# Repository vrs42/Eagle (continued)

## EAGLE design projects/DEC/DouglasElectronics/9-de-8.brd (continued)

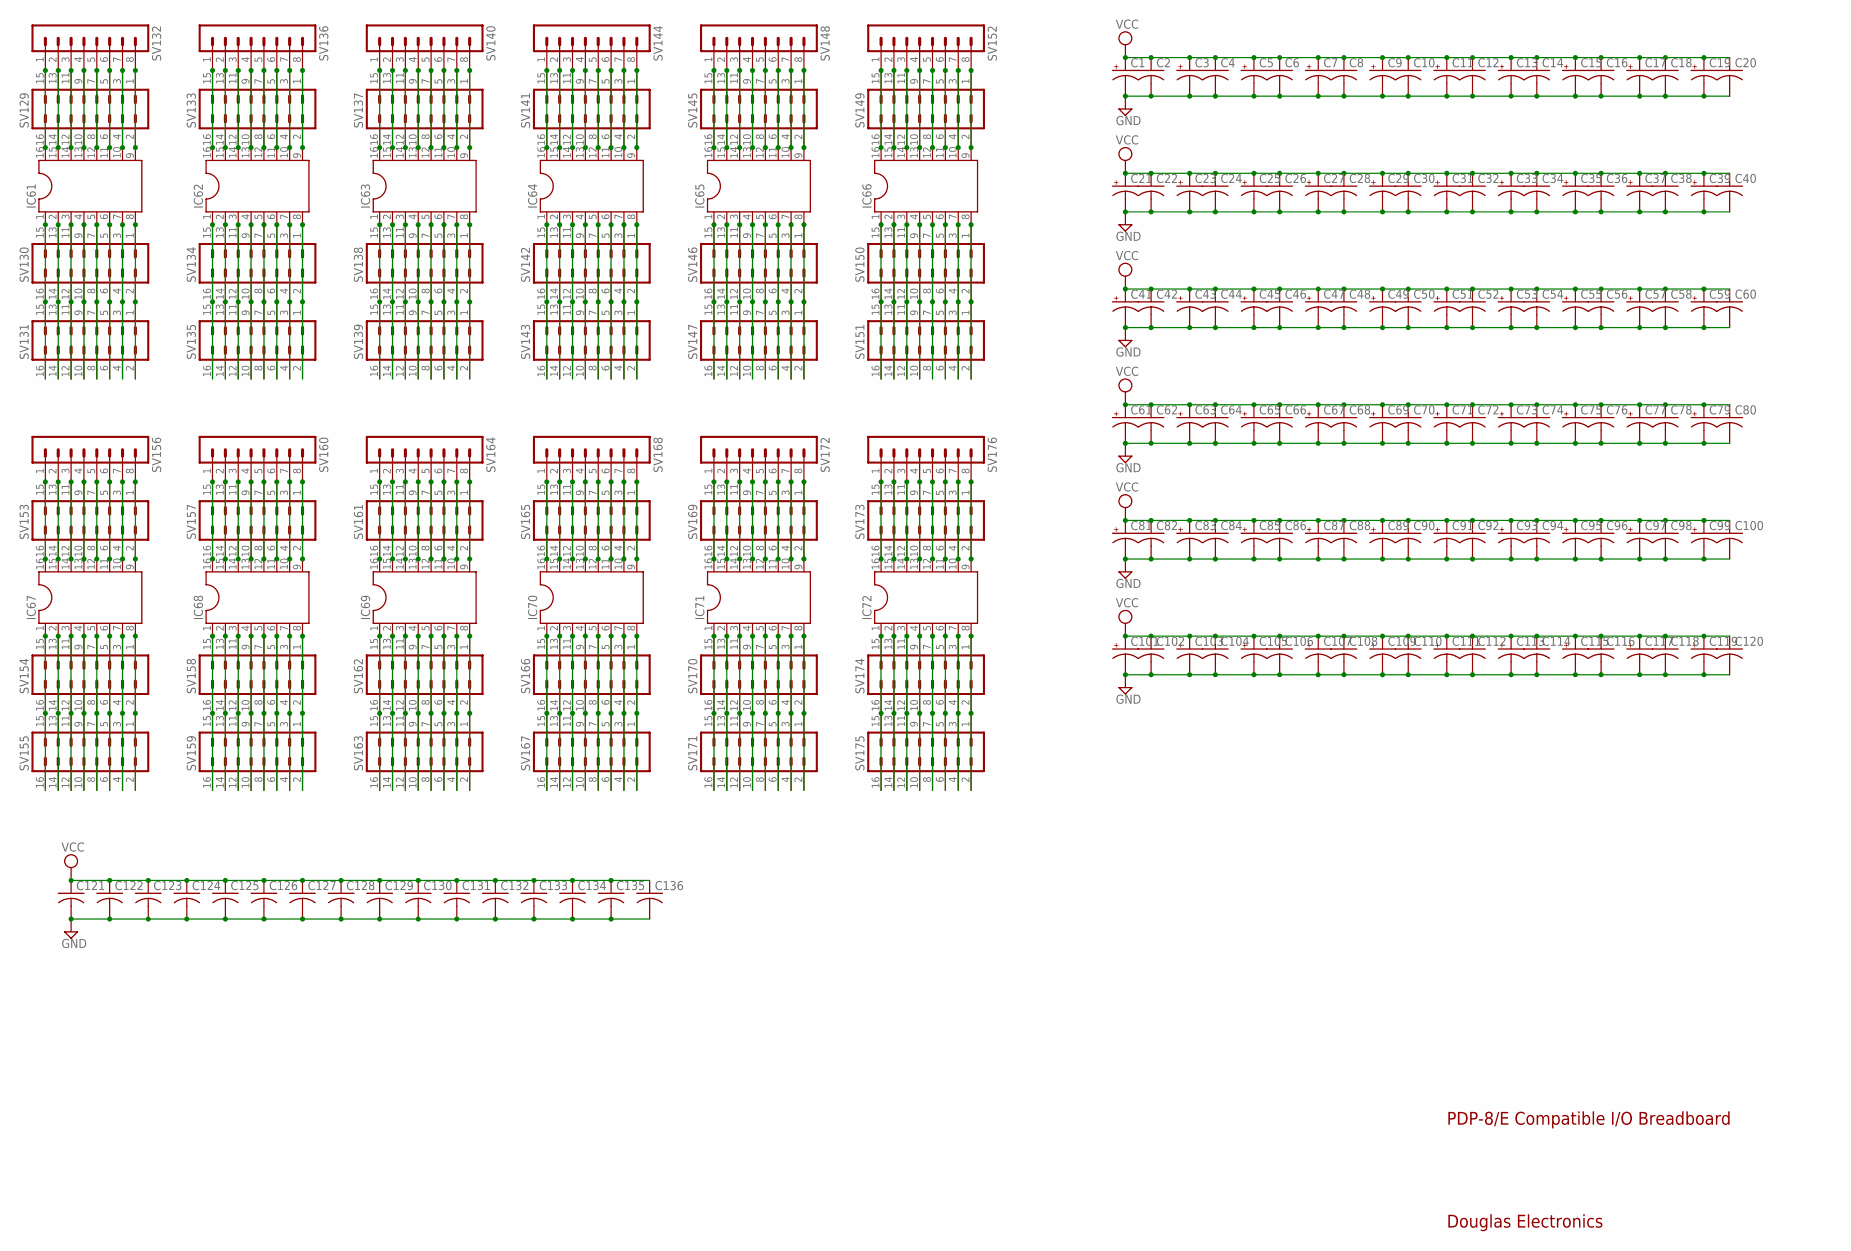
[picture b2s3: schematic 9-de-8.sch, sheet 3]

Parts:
C1, C3, C5, C7, C9, C11, C13, C15, C17, C19, C21, C23, C25, C27, C29, C31, C33, C35, C37, C39, C41, C43, C45, C47, C49, C51, C53, C55, C57, C59, C61, C63, C65, C67, C69, C71, C73, C75, C77, C79, C81, C83, C85, C87, C89, C91, C93, C95, C97, C99, C101, C103, C105, C107, C109, C111, C113, C115, C117, C119: CPOL-USE12-4AXIAL; E12-4
C2, C4, C6, C8, C10, C12, C14, C16, C18, C20, C22, C24, C26, C28, C30, C32, C34, C36, C38, C40, C42, C44, C46, C48, C50, C52, C54, C56, C58, C60, C62, C64, C66, C68, C70, C72, C74, C76, C78, C80, C82, C84, C86, C88, C90, C92, C94, C96, C98, C100, C102, C104, C106, C108, C110, C112, C114, C116, C118, C120: C-US050-025X075; C050-025X075
C121, C122, C123, C124, C125, C126, C127, C128, C129, C130, C131, C132, C133, C134, C135, C136: C-US075-032X103; C075-032X103
IC61, IC62, IC63, IC64, IC65, IC66, IC67, IC68, IC69, IC70, IC71, IC72: DIL16
SV129, SV130, SV131, SV133, SV134, SV135, SV137, SV138, SV139, SV141, SV142, SV143, SV145, SV146, SV147, SV149, SV150, SV151, SV153, SV154, SV155, SV157, SV158, SV159, SV161, SV162, SV163, SV165, SV166, SV167, SV169, SV170, SV171, SV173, SV174, SV175: MA08-2
SV132, SV136, SV140, SV144, SV148, SV152, SV156, SV160, SV164, SV168, SV172, SV176: MA08-1

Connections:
GND: C1.-, C2.2, C3.-, C4.2, C5.-, C6.2, C7.-, C8.2, C9.-, C10.2, C11.-, C12.2, C13.-, C14.2, C15.-, C16.2, C17.-, C18.2, C19.-, C20.2, C21.-, C22.2, C23.-, C24.2, C25.-, C26.2, C27.-, C28.2, C29.-, C30.2, C31.-, C32.2, C33.-, C34.2, C35.-, C36.2, C37.-, C38.2, C39.-, C40.2, C41.-, C42.2, C43.-, C44.2, C45.-, C46.2, C47.-, C48.2, C49.-, C50.2, C51.-, C52.2, C53.-, C54.2, C55.-, C56.2, C57.-, C58.2, C59.-, C60.2, C61.-, C62.2, C63.-, C64.2, C65.-, C66.2, C67.-, C68.2, C69.-, C70.2, C71.-, C72.2, C73.-, C74.2, C75.-, C76.2, C77.-, C78.2, C79.-, C80.2, C81.-, C82.2, C83.-, C84.2, C85.-, C86.2, C87.-, C88.2, C89.-, C90.2, C91.-, C92.2, C93.-, C94.2, C95.-, C96.2, C97.-, C98.2, C99.-, C100.2, C101.-, C102.2, C103.-, C104.2, C105.-, C106.2, C107.-, C108.2, C109.-, C110.2, C111.-, C112.2, C113.-, C114.2, C115.-, C116.2, C117.-, C118.2, C119.-, C120.2, C121.2, C122.2, C123.2, C124.2, C125.2, C126.2, C127.2, C128.2, C129.2, C130.2, C131.2, C132.2, C133.2, C134.2, C135.2, C136.2; also elsewhere on the board
unnamed: IC61.9, SV129.1, SV129.2, SV132.8
unnamed: IC62.6, SV134.5, SV134.6, SV135.5, SV135.6
unnamed: IC61.11, SV129.5, SV129.6, SV132.6
unnamed: IC61.12, SV129.7, SV129.8, SV132.5
unnamed: IC61.13, SV129.9, SV129.10, SV132.4
unnamed: IC61.14, SV129.11, SV129.12, SV132.3
unnamed: IC62.16, SV133.15, SV133.16, SV136.1
unnamed: IC61.16, SV129.15, SV129.16, SV132.1
unnamed: IC61.8, SV130.1, SV130.2, SV131.1, SV131.2
unnamed: IC62.15, SV133.13, SV133.14, SV136.2
unnamed: IC61.6, SV130.5, SV130.6, SV131.5, SV131.6
unnamed: IC62.14, SV133.11, SV133.12, SV136.3
unnamed: IC62.13, SV133.9, SV133.10, SV136.4
unnamed: IC62.12, SV133.7, SV133.8, SV136.5
unnamed: IC62.11, SV133.5, SV133.6, SV136.6
unnamed: IC62.10, SV133.3, SV133.4, SV136.7
unnamed: IC62.9, SV133.1, SV133.2, SV136.8
unnamed: IC61.7, SV130.3, SV130.4, SV131.3, SV131.4
unnamed: IC62.1, SV134.15, SV134.16, SV135.15, SV135.16
unnamed: IC61.5, SV130.7, SV130.8, SV131.7, SV131.8
unnamed: IC61.4, SV130.9, SV130.10, SV131.9, SV131.10
unnamed: IC61.3, SV130.11, SV130.12, SV131.11, SV131.12
unnamed: IC61.2, SV130.13, SV130.14, SV131.13, SV131.14
unnamed: IC61.1, SV130.15, SV130.16, SV131.15, SV131.16
unnamed: IC62.8, SV134.1, SV134.2, SV135.1, SV135.2
unnamed: IC61.15, SV129.13, SV129.14, SV132.2
unnamed: IC62.7, SV134.3, SV134.4, SV135.3, SV135.4
unnamed: IC62.5, SV134.7, SV134.8, SV135.7, SV135.8
unnamed: IC62.4, SV134.9, SV134.10, SV135.9, SV135.10
unnamed: IC62.3, SV134.11, SV134.12, SV135.11, SV135.12
unnamed: IC61.10, SV129.3, SV129.4, SV132.7
unnamed: IC62.2, SV134.13, SV134.14, SV135.13, SV135.14
unnamed: IC63.6, SV138.5, SV138.6, SV139.5, SV139.6
unnamed: IC63.16, SV137.15, SV137.16, SV140.1
unnamed: IC63.15, SV137.13, SV137.14, SV140.2
unnamed: IC63.14, SV137.11, SV137.12, SV140.3
unnamed: IC63.13, SV137.9, SV137.10, SV140.4
unnamed: IC63.12, SV137.7, SV137.8, SV140.5
unnamed: IC63.11, SV137.5, SV137.6, SV140.6
unnamed: IC63.10, SV137.3, SV137.4, SV140.7
unnamed: IC63.9, SV137.1, SV137.2, SV140.8
unnamed: IC63.1, SV138.15, SV138.16, SV139.15, SV139.16
unnamed: IC63.8, SV138.1, SV138.2, SV139.1, SV139.2
unnamed: IC63.7, SV138.3, SV138.4, SV139.3, SV139.4
unnamed: IC63.5, SV138.7, SV138.8, SV139.7, SV139.8
unnamed: IC63.4, SV138.9, SV138.10, SV139.9, SV139.10
unnamed: IC63.3, SV138.11, SV138.12, SV139.11, SV139.12
unnamed: IC63.2, SV138.13, SV138.14, SV139.13, SV139.14
unnamed: IC64.6, SV142.5, SV142.6, SV143.5, SV143.6
unnamed: IC64.16, SV141.15, SV141.16, SV144.1
unnamed: IC64.15, SV141.13, SV141.14, SV144.2
unnamed: IC64.14, SV141.11, SV141.12, SV144.3
unnamed: IC64.13, SV141.9, SV141.10, SV144.4
unnamed: IC64.12, SV141.7, SV141.8, SV144.5
unnamed: IC64.11, SV141.5, SV141.6, SV144.6
unnamed: IC64.10, SV141.3, SV141.4, SV144.7
unnamed: IC64.9, SV141.1, SV141.2, SV144.8
unnamed: IC64.1, SV142.15, SV142.16, SV143.15, SV143.16
unnamed: IC64.8, SV142.1, SV142.2, SV143.1, SV143.2
unnamed: IC64.7, SV142.3, SV142.4, SV143.3, SV143.4
unnamed: IC64.5, SV142.7, SV142.8, SV143.7, SV143.8
unnamed: IC64.4, SV142.9, SV142.10, SV143.9, SV143.10
unnamed: IC64.3, SV142.11, SV142.12, SV143.11, SV143.12
unnamed: IC64.2, SV142.13, SV142.14, SV143.13, SV143.14
unnamed: IC65.6, SV146.5, SV146.6, SV147.5, SV147.6
unnamed: IC65.16, SV145.15, SV145.16, SV148.1
unnamed: IC65.15, SV145.13, SV145.14, SV148.2
unnamed: IC65.14, SV145.11, SV145.12, SV148.3
unnamed: IC65.13, SV145.9, SV145.10, SV148.4
unnamed: IC65.12, SV145.7, SV145.8, SV148.5
unnamed: IC65.11, SV145.5, SV145.6, SV148.6
unnamed: IC65.10, SV145.3, SV145.4, SV148.7
unnamed: IC65.9, SV145.1, SV145.2, SV148.8
unnamed: IC65.1, SV146.15, SV146.16, SV147.15, SV147.16
unnamed: IC65.8, SV146.1, SV146.2, SV147.1, SV147.2
unnamed: IC65.7, SV146.3, SV146.4, SV147.3, SV147.4
unnamed: IC65.5, SV146.7, SV146.8, SV147.7, SV147.8
unnamed: IC65.4, SV146.9, SV146.10, SV147.9, SV147.10
unnamed: IC65.3, SV146.11, SV146.12, SV147.11, SV147.12
unnamed: IC65.2, SV146.13, SV146.14, SV147.13, SV147.14
unnamed: IC66.6, SV150.5, SV150.6, SV151.5, SV151.6
unnamed: IC66.16, SV149.15, SV149.16, SV152.1
unnamed: IC66.15, SV149.13, SV149.14, SV152.2
unnamed: IC66.14, SV149.11, SV149.12, SV152.3
unnamed: IC66.13, SV149.9, SV149.10, SV152.4
unnamed: IC66.12, SV149.7, SV149.8, SV152.5
unnamed: IC66.11, SV149.5, SV149.6, SV152.6
unnamed: IC66.10, SV149.3, SV149.4, SV152.7
unnamed: IC66.9, SV149.1, SV149.2, SV152.8
unnamed: IC66.1, SV150.15, SV150.16, SV151.15, SV151.16
unnamed: IC66.8, SV150.1, SV150.2, SV151.1, SV151.2
unnamed: IC66.7, SV150.3, SV150.4, SV151.3, SV151.4
unnamed: IC66.5, SV150.7, SV150.8, SV151.7, SV151.8
unnamed: IC66.4, SV150.9, SV150.10, SV151.9, SV151.10
unnamed: IC66.3, SV150.11, SV150.12, SV151.11, SV151.12
unnamed: IC66.2, SV150.13, SV150.14, SV151.13, SV151.14
unnamed: IC67.6, SV154.5, SV154.6, SV155.5, SV155.6
unnamed: IC67.16, SV153.15, SV153.16, SV156.1
unnamed: IC67.15, SV153.13, SV153.14, SV156.2
unnamed: IC67.14, SV153.11, SV153.12, SV156.3
unnamed: IC67.13, SV153.9, SV153.10, SV156.4
unnamed: IC67.12, SV153.7, SV153.8, SV156.5
unnamed: IC67.11, SV153.5, SV153.6, SV156.6
unnamed: IC67.10, SV153.3, SV153.4, SV156.7
unnamed: IC67.9, SV153.1, SV153.2, SV156.8
unnamed: IC67.1, SV154.15, SV154.16, SV155.15, SV155.16
unnamed: IC67.8, SV154.1, SV154.2, SV155.1, SV155.2
unnamed: IC67.7, SV154.3, SV154.4, SV155.3, SV155.4
unnamed: IC67.5, SV154.7, SV154.8, SV155.7, SV155.8
unnamed: IC67.4, SV154.9, SV154.10, SV155.9, SV155.10
unnamed: IC67.3, SV154.11, SV154.12, SV155.11, SV155.12
unnamed: IC67.2, SV154.13, SV154.14, SV155.13, SV155.14
unnamed: IC68.6, SV158.5, SV158.6, SV159.5, SV159.6
unnamed: IC68.16, SV157.15, SV157.16, SV160.1
unnamed: IC68.15, SV157.13, SV157.14, SV160.2
unnamed: IC68.14, SV157.11, SV157.12, SV160.3
unnamed: IC68.13, SV157.9, SV157.10, SV160.4
unnamed: IC68.12, SV157.7, SV157.8, SV160.5
unnamed: IC68.11, SV157.5, SV157.6, SV160.6
unnamed: IC68.10, SV157.3, SV157.4, SV160.7
unnamed: IC68.9, SV157.1, SV157.2, SV160.8
unnamed: IC68.1, SV158.15, SV158.16, SV159.15, SV159.16
unnamed: IC68.8, SV158.1, SV158.2, SV159.1, SV159.2
unnamed: IC68.7, SV158.3, SV158.4, SV159.3, SV159.4
unnamed: IC68.5, SV158.7, SV158.8, SV159.7, SV159.8
unnamed: IC68.4, SV158.9, SV158.10, SV159.9, SV159.10
unnamed: IC68.3, SV158.11, SV158.12, SV159.11, SV159.12
unnamed: IC68.2, SV158.13, SV158.14, SV159.13, SV159.14
unnamed: IC69.6, SV162.5, SV162.6, SV163.5, SV163.6
unnamed: IC69.16, SV161.15, SV161.16, SV164.1
unnamed: IC69.15, SV161.13, SV161.14, SV164.2
unnamed: IC69.14, SV161.11, SV161.12, SV164.3
unnamed: IC69.13, SV161.9, SV161.10, SV164.4
unnamed: IC69.12, SV161.7, SV161.8, SV164.5
unnamed: IC69.11, SV161.5, SV161.6, SV164.6
unnamed: IC69.10, SV161.3, SV161.4, SV164.7
unnamed: IC69.9, SV161.1, SV161.2, SV164.8
unnamed: IC69.1, SV162.15, SV162.16, SV163.15, SV163.16
unnamed: IC69.8, SV162.1, SV162.2, SV163.1, SV163.2
unnamed: IC69.7, SV162.3, SV162.4, SV163.3, SV163.4
unnamed: IC69.5, SV162.7, SV162.8, SV163.7, SV163.8
unnamed: IC69.4, SV162.9, SV162.10, SV163.9, SV163.10
unnamed: IC69.3, SV162.11, SV162.12, SV163.11, SV163.12
unnamed: IC69.2, SV162.13, SV162.14, SV163.13, SV163.14
unnamed: IC70.6, SV166.5, SV166.6, SV167.5, SV167.6
unnamed: IC70.16, SV165.15, SV165.16, SV168.1
unnamed: IC70.15, SV165.13, SV165.14, SV168.2
unnamed: IC70.14, SV165.11, SV165.12, SV168.3
unnamed: IC70.13, SV165.9, SV165.10, SV168.4
unnamed: IC70.12, SV165.7, SV165.8, SV168.5
unnamed: IC70.11, SV165.5, SV165.6, SV168.6
unnamed: IC70.10, SV165.3, SV165.4, SV168.7
unnamed: IC70.9, SV165.1, SV165.2, SV168.8
unnamed: IC70.1, SV166.15, SV166.16, SV167.15, SV167.16
unnamed: IC70.8, SV166.1, SV166.2, SV167.1, SV167.2
unnamed: IC70.7, SV166.3, SV166.4, SV167.3, SV167.4
unnamed: IC70.5, SV166.7, SV166.8, SV167.7, SV167.8
unnamed: IC70.4, SV166.9, SV166.10, SV167.9, SV167.10
unnamed: IC70.3, SV166.11, SV166.12, SV167.11, SV167.12
unnamed: IC70.2, SV166.13, SV166.14, SV167.13, SV167.14
unnamed: IC71.6, SV170.5, SV170.6, SV171.5, SV171.6
unnamed: IC71.16, SV169.15, SV169.16, SV172.1
unnamed: IC71.15, SV169.13, SV169.14, SV172.2
unnamed: IC71.14, SV169.11, SV169.12, SV172.3
unnamed: IC71.13, SV169.9, SV169.10, SV172.4
unnamed: IC71.12, SV169.7, SV169.8, SV172.5
unnamed: IC71.11, SV169.5, SV169.6, SV172.6
unnamed: IC71.10, SV169.3, SV169.4, SV172.7
unnamed: IC71.9, SV169.1, SV169.2, SV172.8
unnamed: IC71.1, SV170.15, SV170.16, SV171.15, SV171.16
unnamed: IC71.8, SV170.1, SV170.2, SV171.1, SV171.2
unnamed: IC71.7, SV170.3, SV170.4, SV171.3, SV171.4
unnamed: IC71.5, SV170.7, SV170.8, SV171.7, SV171.8
unnamed: IC71.4, SV170.9, SV170.10, SV171.9, SV171.10
unnamed: IC71.3, SV170.11, SV170.12, SV171.11, SV171.12
unnamed: IC71.2, SV170.13, SV170.14, SV171.13, SV171.14
unnamed: IC72.6, SV174.5, SV174.6, SV175.5, SV175.6
unnamed: IC72.16, SV173.15, SV173.16, SV176.1
unnamed: IC72.15, SV173.13, SV173.14, SV176.2
unnamed: IC72.14, SV173.11, SV173.12, SV176.3
unnamed: IC72.13, SV173.9, SV173.10, SV176.4
unnamed: IC72.12, SV173.7, SV173.8, SV176.5
unnamed: IC72.11, SV173.5, SV173.6, SV176.6
unnamed: IC72.10, SV173.3, SV173.4, SV176.7
unnamed: IC72.9, SV173.1, SV173.2, SV176.8
unnamed: IC72.1, SV174.15, SV174.16, SV175.15, SV175.16
unnamed: IC72.8, SV174.1, SV174.2, SV175.1, SV175.2
unnamed: IC72.7, SV174.3, SV174.4, SV175.3, SV175.4
unnamed: IC72.5, SV174.7, SV174.8, SV175.7, SV175.8
unnamed: IC72.4, SV174.9, SV174.10, SV175.9, SV175.10
unnamed: IC72.3, SV174.11, SV174.12, SV175.11, SV175.12
unnamed: IC72.2, SV174.13, SV174.14, SV175.13, SV175.14
VCC: C1.+, C2.1, C3.+, C4.1, C5.+, C6.1, C7.+, C8.1, C9.+, C10.1, C11.+, C12.1, C13.+, C14.1, C15.+, C16.1, C17.+, C18.1, C19.+, C20.1, C21.+, C22.1, C23.+, C24.1, C25.+, C26.1, C27.+, C28.1, C29.+, C30.1, C31.+, C32.1, C33.+, C34.1, C35.+, C36.1, C37.+, C38.1, C39.+, C40.1, C41.+, C42.1, C43.+, C44.1, C45.+, C46.1, C47.+, C48.1, C49.+, C50.1, C51.+, C52.1, C53.+, C54.1, C55.+, C56.1, C57.+, C58.1, C59.+, C60.1, C61.+, C62.1, C63.+, C64.1, C65.+, C66.1, C67.+, C68.1, C69.+, C70.1, C71.+, C72.1, C73.+, C74.1, C75.+, C76.1, C77.+, C78.1, C79.+, C80.1, C81.+, C82.1, C83.+, C84.1, C85.+, C86.1, C87.+, C88.1, C89.+, C90.1, C91.+, C92.1, C93.+, C94.1, C95.+, C96.1, C97.+, C98.1, C99.+, C100.1, C101.+, C102.1, C103.+, C104.1, C105.+, C106.1, C107.+, C108.1, C109.+, C110.1, C111.+, C112.1, C113.+, C114.1, C115.+, C116.1, C117.+, C118.1, C119.+, C120.1, C121.1, C122.1, C123.1, C124.1, C125.1, C126.1, C127.1, C128.1, C129.1, C130.1, C131.1, C132.1, C133.1, C134.1, C135.1, C136.1; also elsewhere on the board

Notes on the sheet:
PDP-8/E Compatible I/O Breadboard
Douglas Electronics

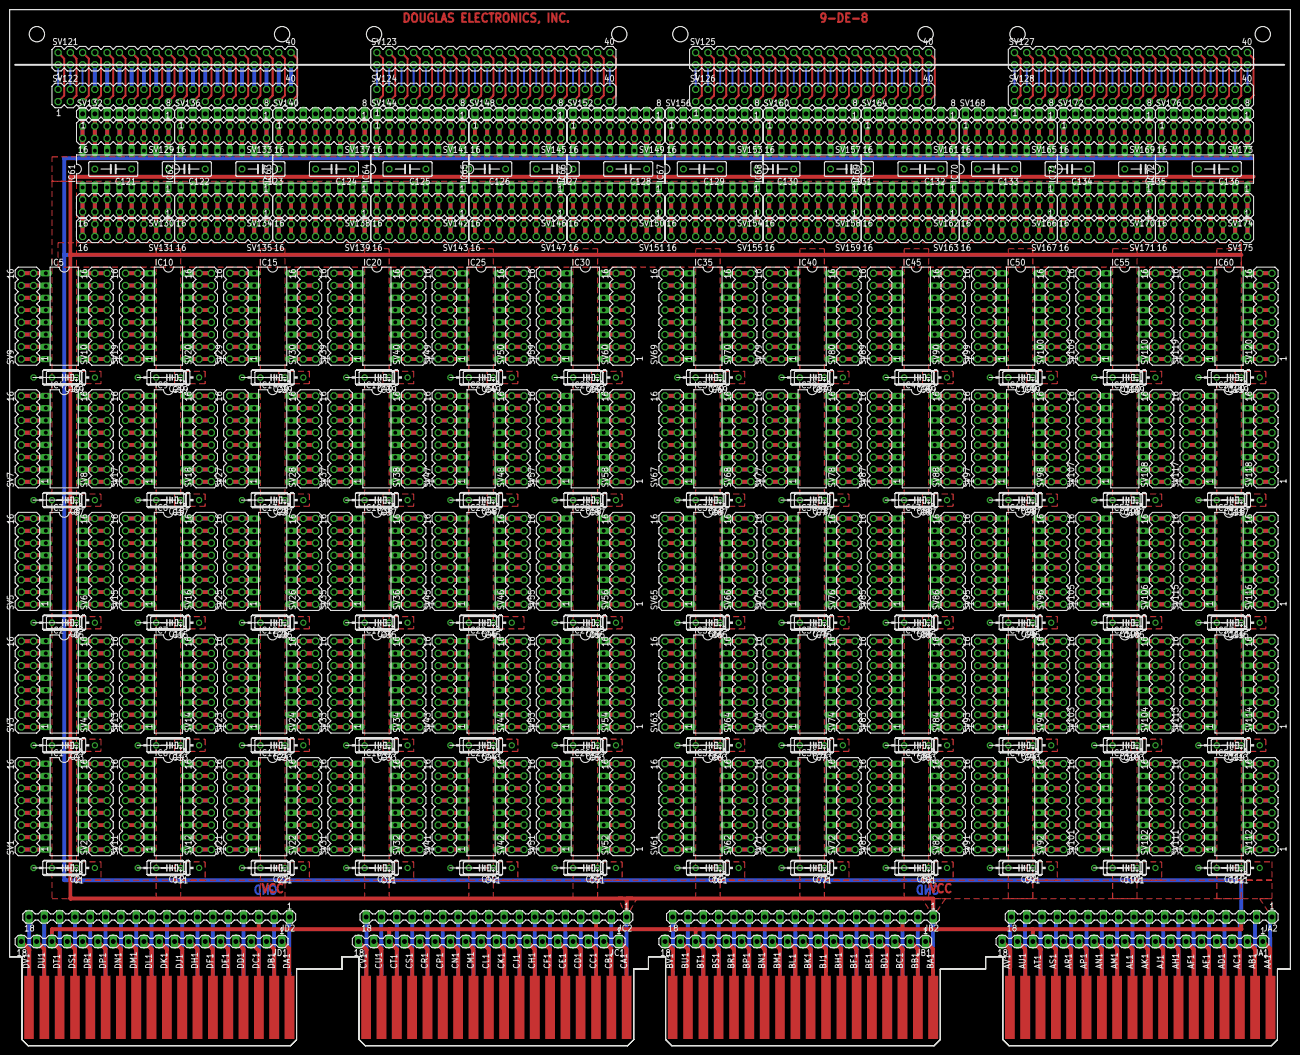
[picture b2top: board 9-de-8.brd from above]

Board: 2 copper layers, 265.3 x 214.6 mm, 394 parts (0 on the bottom side), 1447 nets.

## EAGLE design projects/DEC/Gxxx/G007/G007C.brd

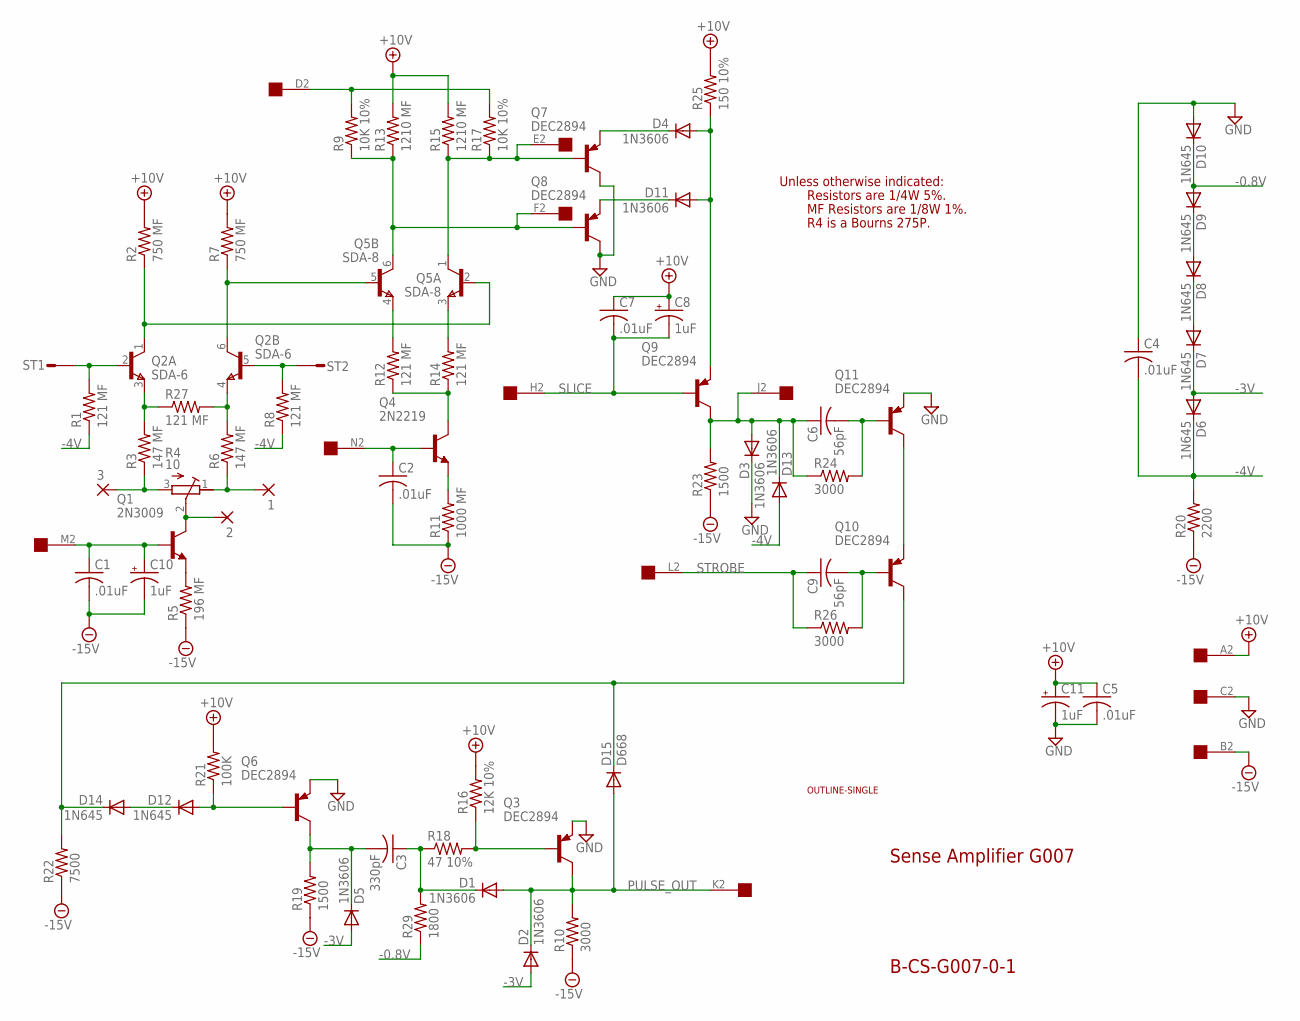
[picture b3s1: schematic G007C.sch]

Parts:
1, 2, 3: 2,54/0,8
C1, C2, C4, C5, C7: .01uF; C050-025X075
C3: 330pF; C075-032X103
C6, C9: 56pF; C075-032X103
C8, C10, C11: 1uF; E12-4
D1, D2, D3, D4, D5, D11, D13: 1N3606; DO35-10
D6, D7, D8, D9, D10, D12, D14: 1N645; DO35-10
D15: D668; DO35-10
Q1: 2N3009; TO5
Q2: SDA-6; TO78
Q3, Q6, Q7, Q8, Q9, Q10, Q11: DEC2894; TO39
Q4: 2N2219; TO5
Q5: SDA-8; TO78
R1, R8, R12, R14, R27: 121 MF; 0207/12
R2, R7: 750 MF; 0207/12
R3, R6: 147 MF; 0207/12
R4: 10; 3006Y
R5: 196 MF; 0207/12
R9, R17: 10K 10%; 0207/10
R10, R24, R26: 3000; 0207/10
R11: 1000 MF; 0207/12
R13, R15: 1210 MF; 0207/12
R16: 12K 10%; 0207/10
R18: 47 10%; 0207/10
R19, R23: 1500; 0207/10
R20: 2200; 0207/10
R21: 100K; 0207/10
R22: 7500; 0207/10
R25: 150 10%; 0207/10
R29: 1800; 0207/10
ST1, ST2: ST2,8
U$1: OUTLINE-SINGLE; SINGLE
U$2: EDGE-1; EDGE-CON1

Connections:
+10V: C5.1, C7.1, C8.+, C11.+, R2.2, R7.2, R13.2, R15.2, R16.2, R21.2, R25.2, U$2.A2
-0.8V: D9.A, D10.C, R29.1
-3V: D2.A, D5.A, D6.A, D7.C
-4V: C4.2, D6.C, D13.A, R1.1, R8.1, R20.2
-15V: C1.2, C2.2, C10.-, R5.1, R10.1, R11.1, R19.1, R20.1, R22.1, R23.1, U$2.B2
GND: C4.1, C5.2, C11.-, D3.C, D10.A, Q3.1 (E), Q6.1 (E), Q7.3 (C), Q8.3 (C), Q11.1 (E), U$2.C2
unnamed: D4.C, Q7.1 (E)
unnamed: C6.1, D3.A, D13.C, Q9.3 (C), R23.2, R24.1, U$2.J2
unnamed: D11.C, Q8.1 (E)
unnamed: Q4.3 (C), R12.1, R14.1
unnamed: C2.1, Q4.2 (B), U$2.N2
unnamed: D4.A, D11.A, Q9.1 (E), R25.1
unnamed: Q5.4 (E), R12.2
unnamed: Q5.6 (C), Q8.2 (B), R9.1, R13.1, U$2.F2
unnamed: Q5.3 (E), R14.2
unnamed: Q2.1 (C), Q5.2 (B), R2.1
unnamed: Q10.1 (E), Q11.3 (C)
unnamed: C1.1, C10.+, Q1.2 (B), U$2.M2
unnamed: D14.C, D15.C, Q10.3 (C), R22.2
unnamed: D8.A, D9.C
unnamed: R9.2, R17.2, U$2.D2
unnamed: C9.2, Q10.2 (B), R26.2
unnamed: Q4.1 (E), R11.2
unnamed: D12.C, D14.A
unnamed: Q5.1 (C), Q7.2 (B), R15.1, R17.1, U$2.E2
unnamed: C6.2, Q11.2 (B), R24.2
unnamed: D12.A, Q6.2 (B), R21.1
unnamed: C3.2, D5.C, Q6.3 (C), R19.2
unnamed: Q3.2 (B), R16.1, R18.2
unnamed: C3.1, D1.C, R18.1, R29.2
unnamed: D7.A, D8.C
unnamed: Q2.6 (C), Q5.5 (B), R7.1
unnamed: Q2.2 (B), R1.2, ST1.1
unnamed: Q2.5 (B), R8.2, ST2.1
unnamed: Q2.3 (E), R3.2, R27.1
unnamed: Q2.4 (E), R6.2, R27.2
unnamed: 3.1, R3.1, R4.3 (E)
unnamed: 1.1, R4.1 (A), R6.1
unnamed: 2.1, Q1.3 (C), R4.2 (S)
unnamed: Q1.1 (E), R5.2
PULSE_OUT: D1.A, D2.C, D15.A, Q3.3 (C), R10.2, U$2.K2
SLICE: C7.2, C8.-, Q9.2 (B), U$2.H2
STROBE: C9.1, R26.1, U$2.L2

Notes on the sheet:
Sense Amplifier G007
B-CS-G007-0-1
Unless otherwise indicated:
Resistors are 1/4W 5%.
MF Resistors are 1/8W 1%.
R4 is a Bourns 275P.

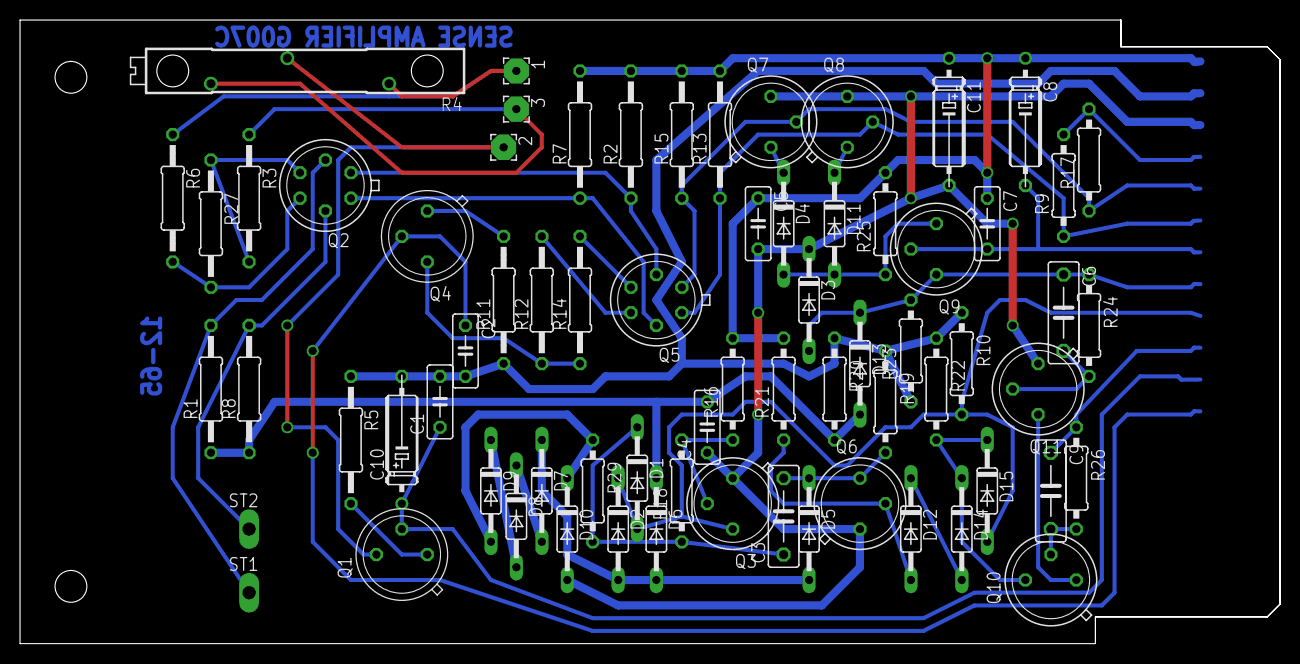
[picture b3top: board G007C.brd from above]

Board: 2 copper layers, 125.7 x 62.2 mm, 72 parts (0 on the bottom side), 43 nets.

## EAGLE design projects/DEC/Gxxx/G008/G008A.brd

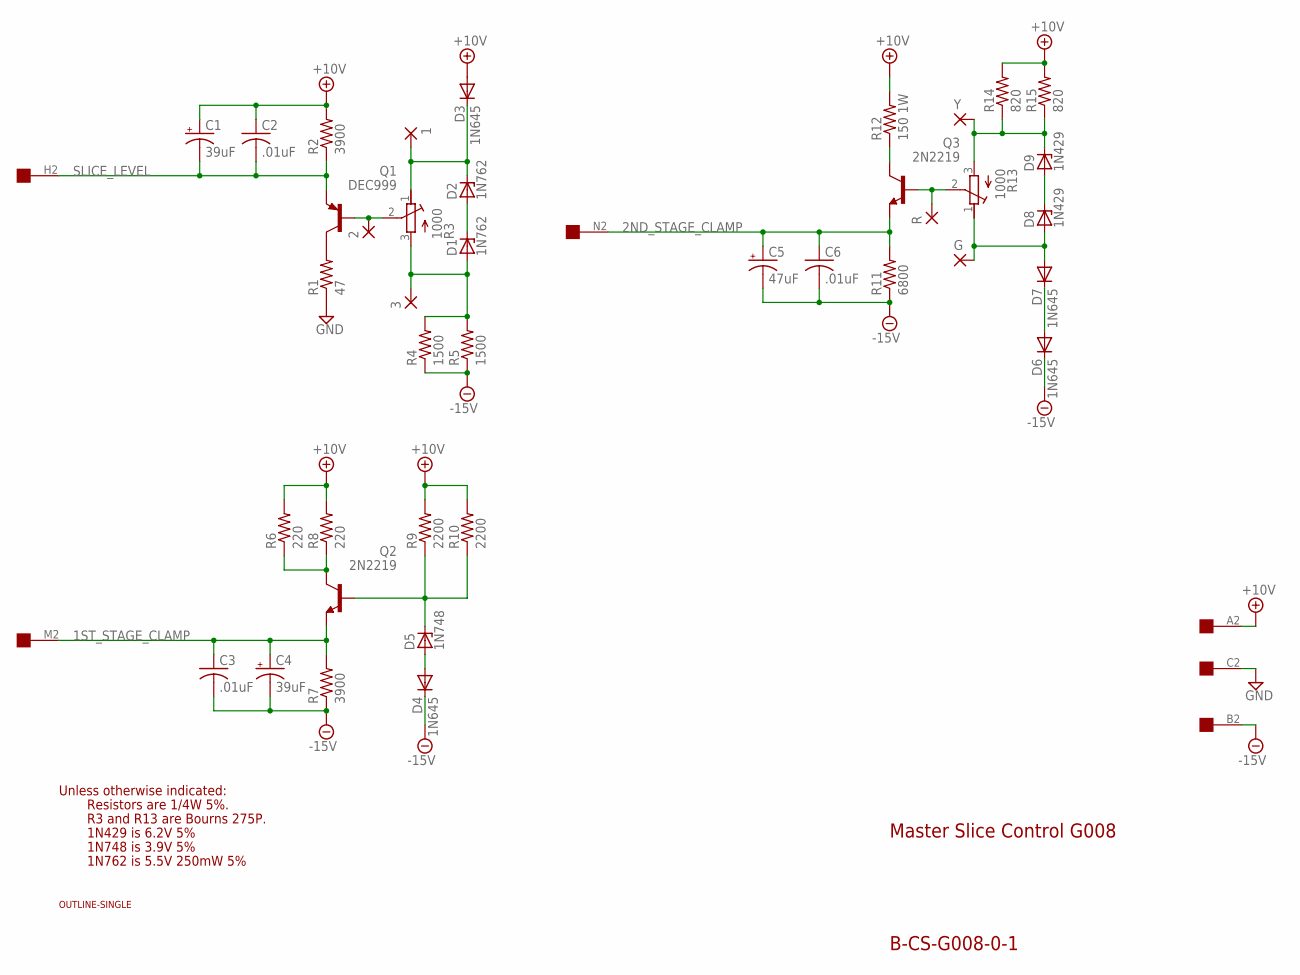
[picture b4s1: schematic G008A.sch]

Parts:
1, 2, 3: 2,54/0,8
C1, C4: 39uF; E15-5
C2, C3, C6: .01uF; C050-025X075
C5: 47uF; E22-6
D1, D2: 1N762; DO35Z10
D3, D4, D6, D7: 1N645; DO35-10
D5: 1N748; DO35Z10
D8, D9: 1N429; DO35Z10
G: 2,54/0,8
Q1: DEC999; TO39
Q2, Q3: 2N2219; TO5
R: 2,54/0,8
R1: 47; 0207/10
R2, R7: 3900; 0207/10
R3, R13: 1000; 3006Y
R4, R5: 1500; 0207/10
R6, R8: 220; 0207/10
R9, R10: 2200; 0207/10
R11: 6800; 0207/10
R12: 150 1W; 0617/22
R14, R15: 820; 0207/10
U$1: OUTLINE-SINGLE; SINGLE
U$2: EDGE-1; EDGE-CON1
Y: 2,54/0,8

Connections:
1ST_STAGE_CLAMP: C3.1, C4.+, Q2.1 (E), R7.2, U$2.M2
2ND_STAGE_CLAMP: C5.+, C6.1, Q3.1 (E), R11.2, U$2.N2
+10V: C1.+, C2.1, D3.A, R2.2, R6.2, R8.2, R9.2, R10.2, R12.2, R14.2, R15.2, U$2.A2
-15V: C3.2, C4.-, C5.-, C6.2, D4.C, D6.C, R4.1, R5.1, R7.1, R11.1, U$2.B2
GND: R1.1, U$2.C2
unnamed: 3.1, D1.A, R3.3 (E), R4.2, R5.2
unnamed: Q2.3 (C), R6.1, R8.1
unnamed: D1.C, D2.A
unnamed: Q1.3 (C), R1.2
unnamed: D4.A, D5.A
unnamed: Q3.3 (C), R12.1
unnamed: D5.C, Q2.2 (B), R9.1, R10.1
unnamed: Q3.2 (B), R.1, R13.2 (S)
unnamed: D6.A, D7.C
unnamed: D7.A, D8.A, G.1, R13.1 (A)
unnamed: D8.C, D9.A
unnamed: D9.C, R13.3 (E), R14.1, R15.1, Y.1
unnamed: 1.1, D2.C, D3.C, R3.1 (A)
unnamed: 2.1, Q1.2 (B), R3.2 (S)
SLICE_LEVEL: C1.-, C2.2, Q1.1 (E), R2.1, U$2.H2

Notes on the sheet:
Master Slice Control G008
B-CS-G008-0-1
Unless otherwise indicated:
Resistors are 1/4W 5%.
R3 and R13 are Bourns 275P.
1N429 is 6.2V 5%
1N748 is 3.9V 5%
1N762 is 5.5V 250mW 5%

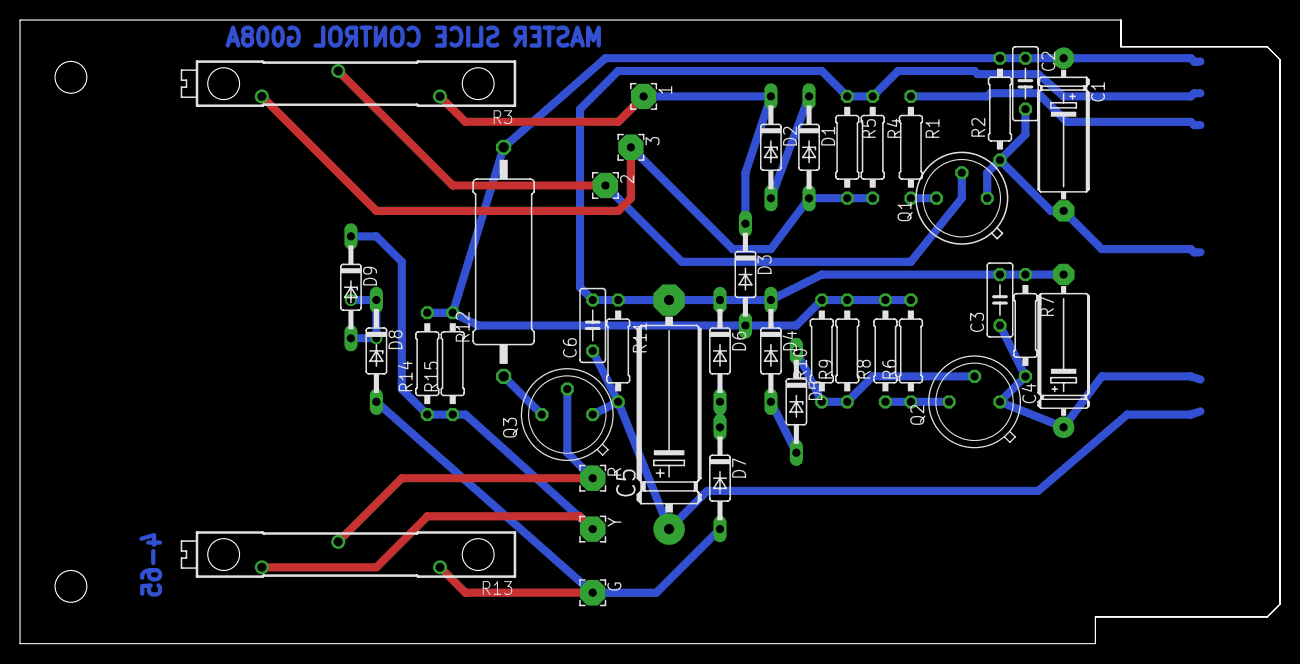
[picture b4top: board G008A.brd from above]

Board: 2 copper layers, 125.7 x 62.2 mm, 41 parts (0 on the bottom side), 20 nets.

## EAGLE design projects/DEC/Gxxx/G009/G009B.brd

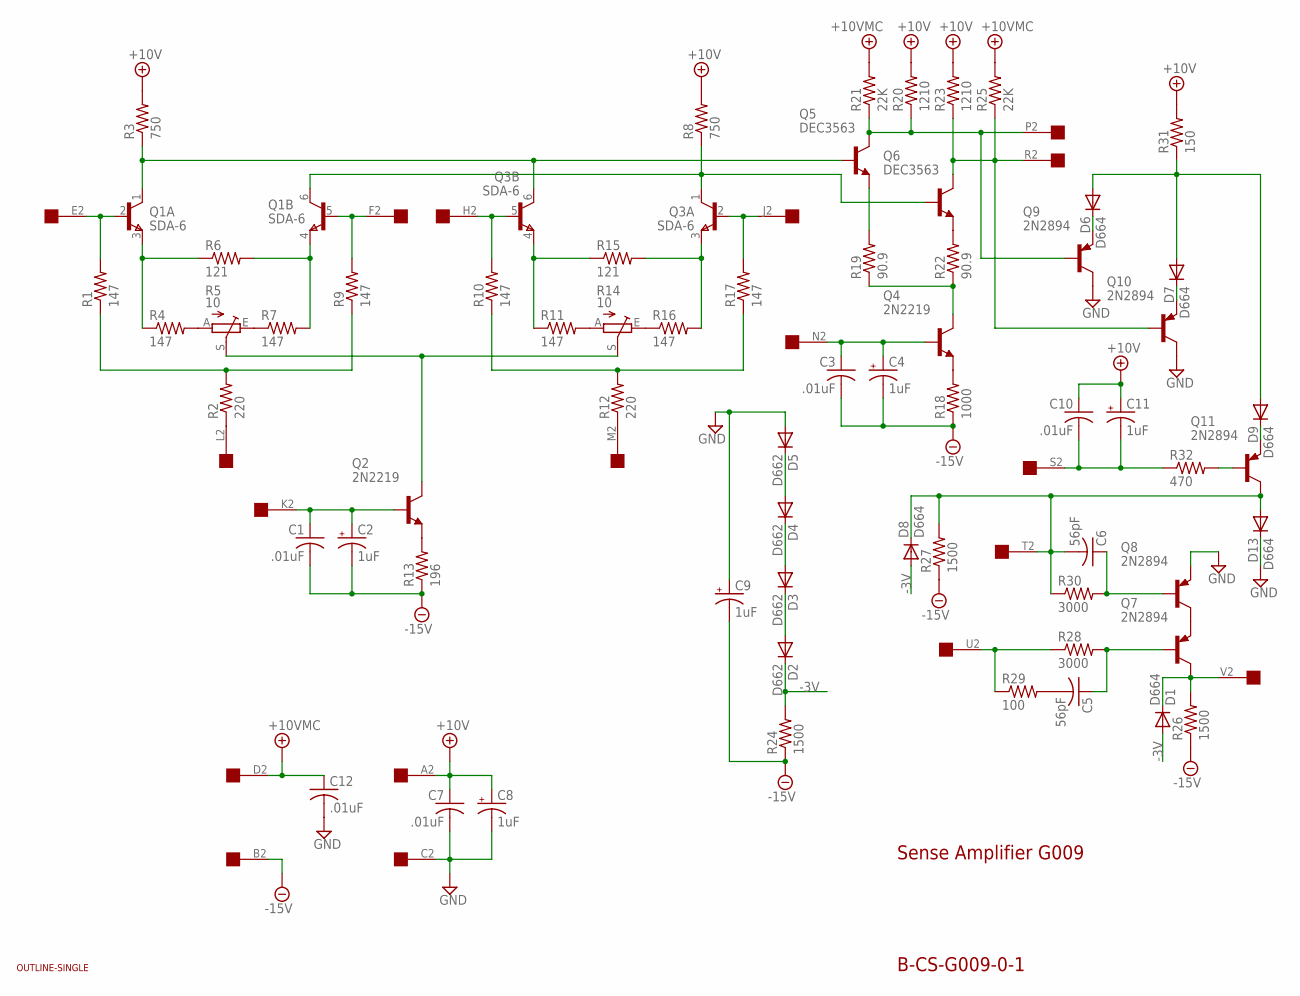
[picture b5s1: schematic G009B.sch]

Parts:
C1, C3, C7, C10, C12: .01uF; C063-025X075
C2, C4, C8, C9, C11: 1uF; E15-5
C5, C6: 56pF; C150-054X183
D1, D6, D7, D8, D9, D13: D664; DO35-10
D2, D3, D4, D5: D662; DO35-10
Q1, Q3: SDA-6; TO78
Q2, Q4: 2N2219; TO5
Q5, Q6: DEC3563; TO5
Q7, Q8, Q9, Q10, Q11: 2N2894; TO5
R1, R4, R7, R9, R10, R11, R16, R17: 147; 0207/15
R2, R12: 220; 0207/10
R3, R8: 750; 0207/15
R5, R14: 10; CT6
R6, R15: 121; 0207/15
R13: 196; 0207/15
R18: 1000; 0207/15
R19, R22: 90.9; 0207/15
R20, R23: 1210; 0207/15
R21, R25: 22K; 0207/10
R24, R26, R27: 1500; 0207/10
R28, R30: 3000; 0207/10
R29: 100; 0207/10
R31: 150; 0207/10
R32: 470; 0207/10
U$1: OUTLINE-SINGLE; SINGLE
U$2: EDGE-1; EDGE-CON1

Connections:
+10V: C7.1, C8.+, C10.1, C11.+, R3.2, R8.2, R20.2, R23.2, R31.2, U$2.A2
+10VMC: C12.1, R21.2, R25.2, U$2.D2
-3V: D1.A, D2.C, D8.A, R24.2
-15V: C1.2, C2.-, C3.2, C4.-, C9.-, R13.1, R18.1, R24.1, R26.1, R27.1, U$2.B2
GND: C7.2, C8.-, C9.+, C12.2, D5.A, D13.C, Q8.1 (E), Q9.3 (C), Q10.3 (C), U$2.C2
unnamed: Q1.2 (B), R1.2, U$2.E2
unnamed: R2.1, U$2.L2
unnamed: R1.1, R2.2, R9.1
unnamed: Q1.5 (B), R9.2, U$2.F2
unnamed: Q1.1 (C), Q3.6 (C), Q5.2 (B), R3.1
unnamed: Q1.6 (C), Q3.1 (C), Q6.2 (B), R8.1
unnamed: Q1.3 (E), R4.1, R6.1
unnamed: Q1.4 (E), R6.2, R7.2
unnamed: R4.2, R5.A
unnamed: R5.E, R7.1
unnamed: Q3.5 (B), R10.2, U$2.H2
unnamed: R10.1, R12.2, R17.1
unnamed: Q3.2 (B), R17.2, U$2.J2
unnamed: Q2.1 (E), R13.2
unnamed: C1.1, C2.+, Q2.2 (B), U$2.K2
unnamed: Q3.4 (E), R11.1, R15.1
unnamed: Q3.3 (E), R15.2, R16.2
unnamed: R11.2, R14.A
unnamed: R14.E, R16.1
unnamed: R12.1, U$2.M2
unnamed: Q2.3 (C), R5.S, R14.S
unnamed: Q5.3 (C), Q9.2 (B), R20.1, R21.1, U$2.P2
unnamed: Q4.1 (E), R18.2
unnamed: Q6.1 (E), R22.2
unnamed: Q5.1 (E), R19.2
unnamed: Q4.3 (C), R19.1, R22.1
unnamed: Q6.3 (C), Q10.2 (B), R23.1, R25.1, U$2.R2
unnamed: C3.1, C4.+, Q4.2 (B), U$2.N2
unnamed: Q7.1 (E), Q8.3 (C)
unnamed: D2.A, D3.C
unnamed: D3.A, D4.C
unnamed: D4.A, D5.C
unnamed: C10.2, C11.-, R32.1, U$2.S2
unnamed: D6.C, Q9.1 (E)
unnamed: D7.C, Q10.1 (E)
unnamed: D6.A, D7.A, D9.A, R31.1
unnamed: D9.C, Q11.1 (E)
unnamed: C6.2, D8.C, D13.A, Q11.3 (C), R27.2, R30.1, U$2.T2
unnamed: Q11.2 (B), R32.2
unnamed: C5.1, Q7.2 (B), R28.2
unnamed: C5.2, R29.2
unnamed: R28.1, R29.1, U$2.U2
unnamed: C6.1, Q8.2 (B), R30.2
unnamed: D1.C, Q7.3 (C), R26.2, U$2.V2

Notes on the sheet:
Sense Amplifier G009
B-CS-G009-0-1

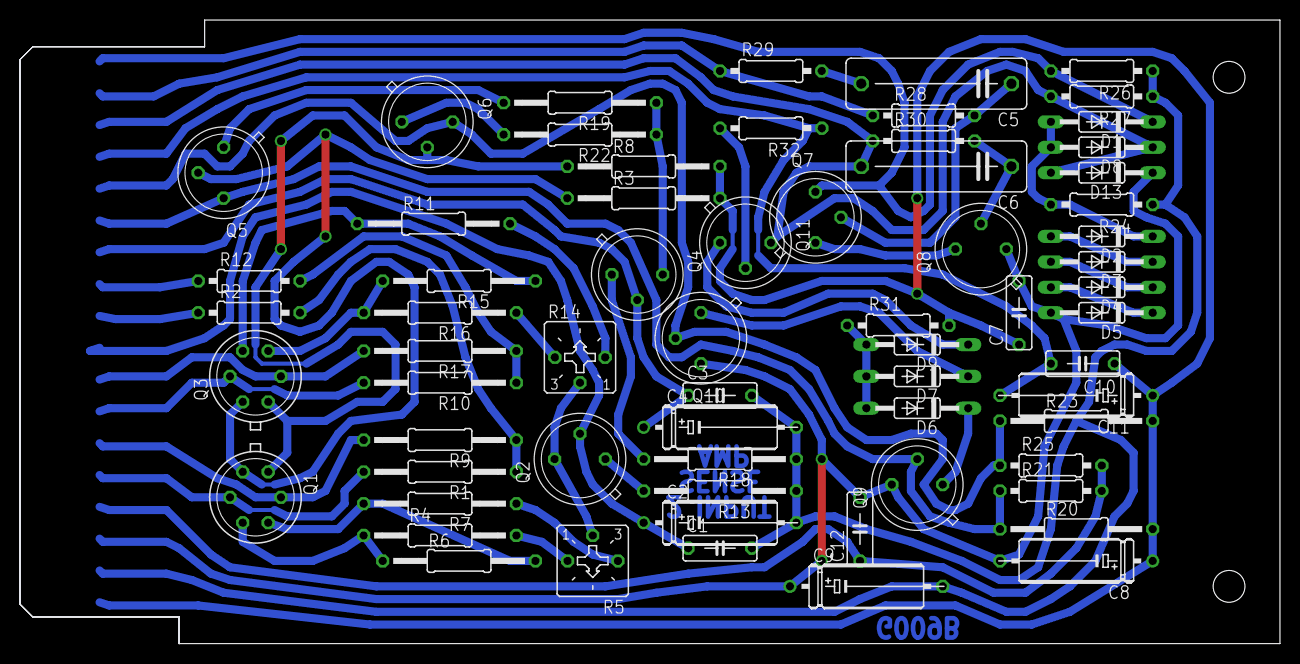
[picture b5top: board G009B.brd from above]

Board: 2 copper layers, 125.7 x 62.2 mm, 67 parts (0 on the bottom side), 49 nets.
